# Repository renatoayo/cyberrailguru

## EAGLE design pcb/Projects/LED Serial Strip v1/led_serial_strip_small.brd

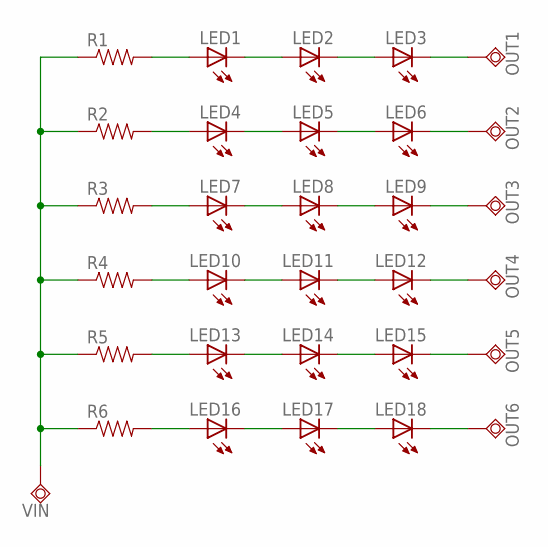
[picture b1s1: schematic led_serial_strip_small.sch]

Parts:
LED1, LED2, LED3, LED4, LED5, LED6, LED7, LED8, LED9, LED10, LED11, LED12, LED13, LED14, LED15, LED16, LED17, LED18: LED0805; LED_0805
OUT1, OUT2, OUT3, OUT4, OUT5, OUT6: TPSQTP15SQ; TP15SQ
R1, R2, R3, R4, R5, R6: RESISTOR0805-RES; 0805
VIN: TPSQTP15SQ; TP15SQ

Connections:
unnamed: LED1.A, R1.2
unnamed: LED1.C, LED2.A
unnamed: LED2.C, LED3.A
unnamed: LED4.A, R2.2
unnamed: LED7.A, R3.2
unnamed: LED10.A, R4.2
unnamed: LED10.C, LED11.A
unnamed: LED11.C, LED12.A
unnamed: LED8.C, LED9.A
unnamed: LED5.C, LED6.A
unnamed: LED4.C, LED5.A
unnamed: LED7.C, LED8.A
unnamed: LED3.C, OUT1.TP
unnamed: LED6.C, OUT2.TP
unnamed: LED9.C, OUT3.TP
unnamed: LED12.C, OUT4.TP
unnamed: LED13.A, R5.2
unnamed: LED16.A, R6.2
unnamed: LED16.C, LED17.A
unnamed: LED17.C, LED18.A
unnamed: LED14.C, LED15.A
unnamed: LED13.C, LED14.A
unnamed: LED15.C, OUT5.TP
unnamed: LED18.C, OUT6.TP
VIN: R1.1, R2.1, R3.1, R4.1, R5.1, R6.1, VIN.TP

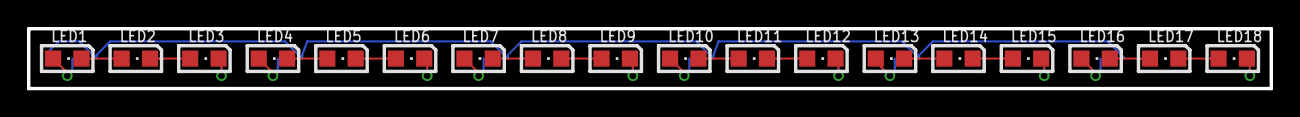
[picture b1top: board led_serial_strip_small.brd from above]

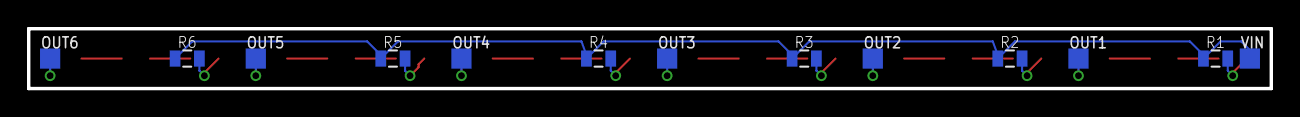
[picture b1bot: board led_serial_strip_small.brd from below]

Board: 2 copper layers, 92.1 x 4.4 mm, 31 parts (13 on the bottom side), 25 nets.

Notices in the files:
parts and their libraries:
SparkFun: Licensing: CC v3.0 Share-Alike You are welcome to use this library for commercial purposes.
